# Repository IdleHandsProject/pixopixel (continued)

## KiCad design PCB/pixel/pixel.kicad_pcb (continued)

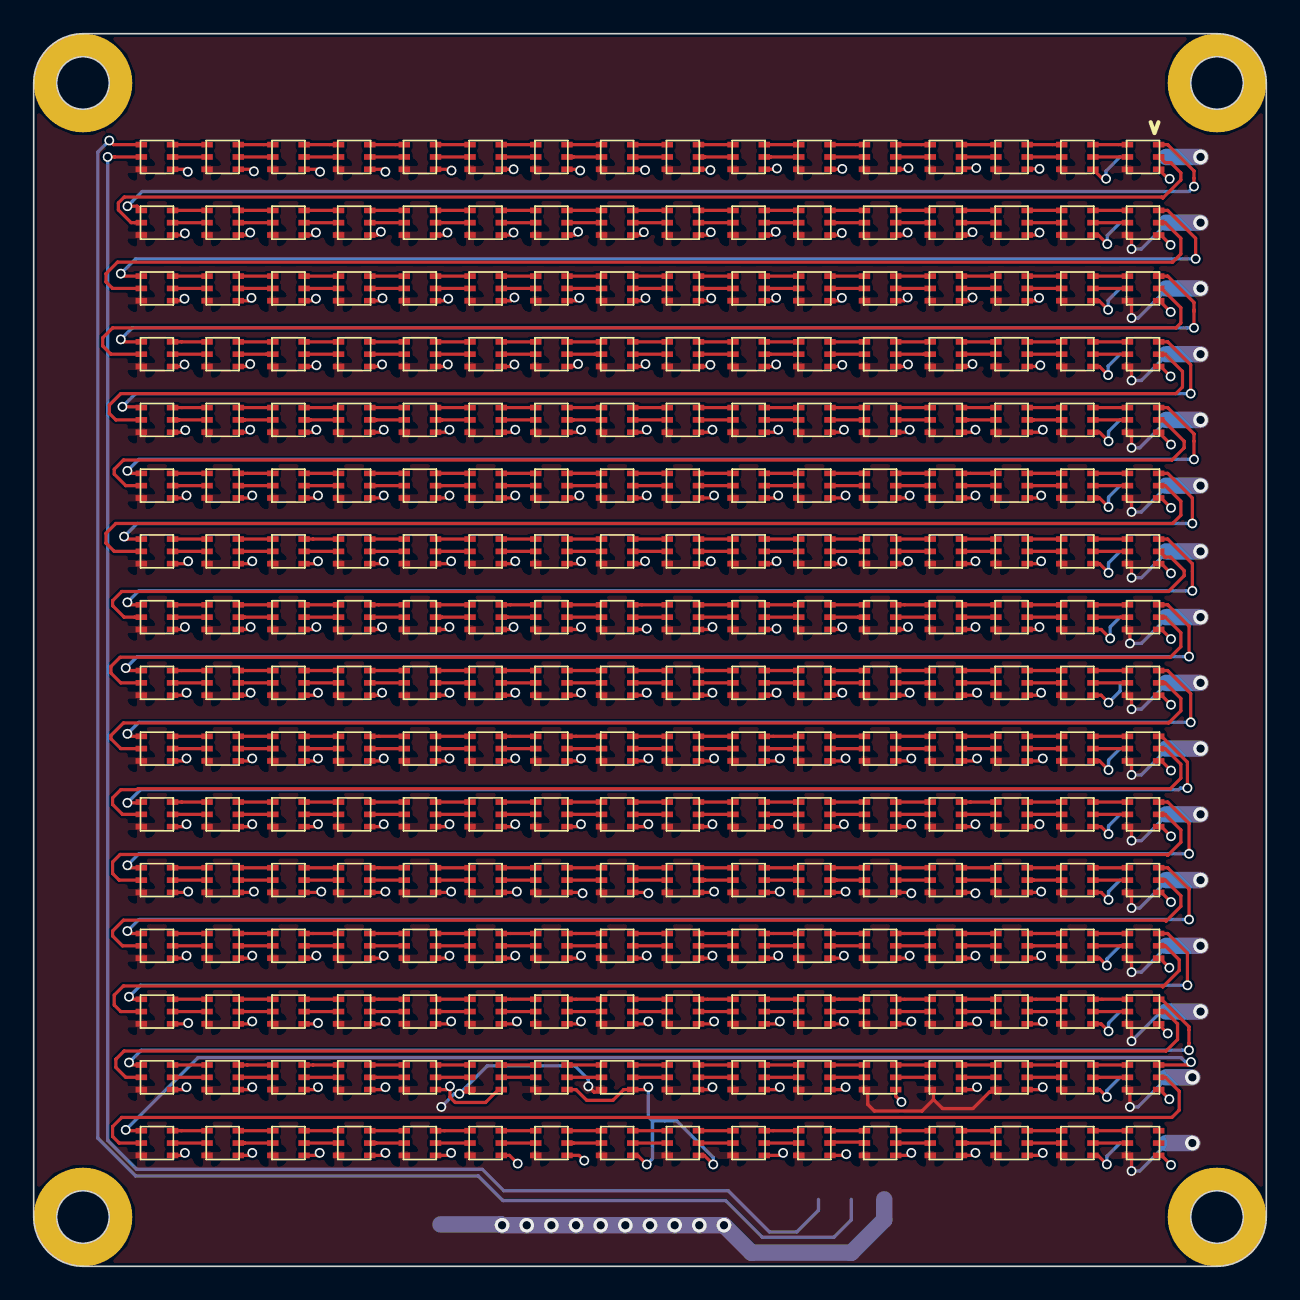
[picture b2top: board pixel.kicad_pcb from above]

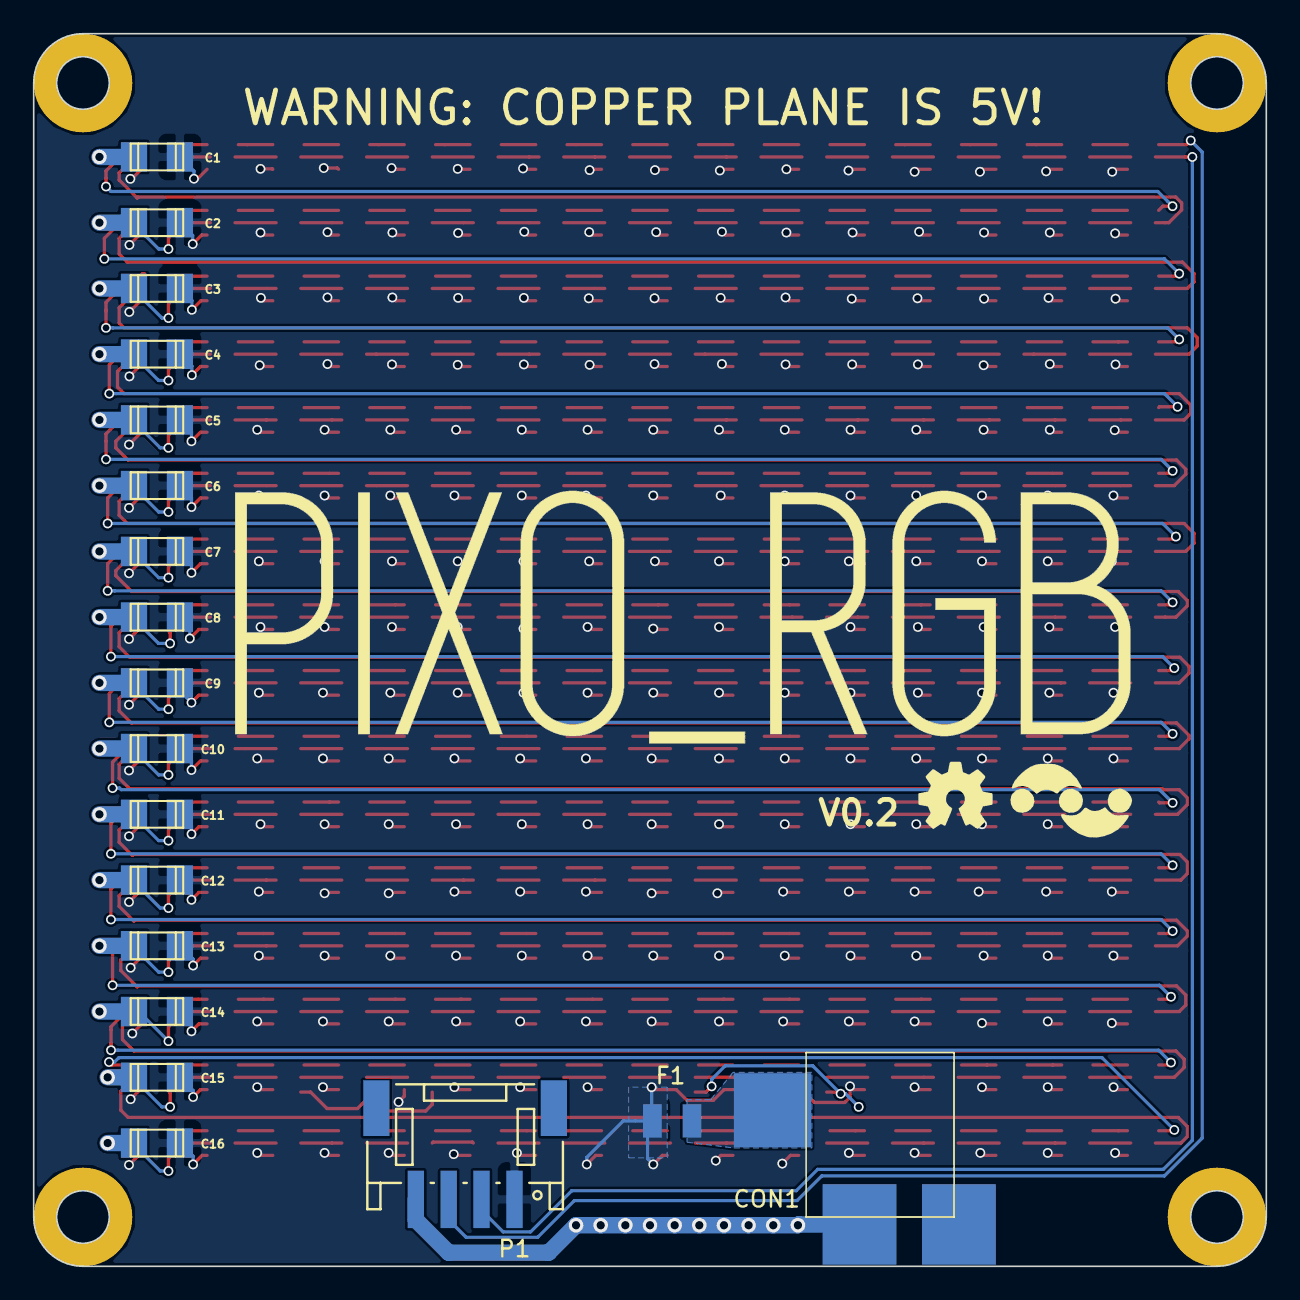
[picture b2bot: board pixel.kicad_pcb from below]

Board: 2 copper layers, 75.0 x 75.0 mm, 275 parts (19 on the bottom side), 515 nets.

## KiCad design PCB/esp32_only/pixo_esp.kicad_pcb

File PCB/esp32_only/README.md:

# ESPEverywhere
ESP8266 Special Make/100 Kickstarter Edition

Check out why this board exists here:
https://www.youtube.com/watch?v=67Kh_ikb-ds

The ESP Everywhere was made to take part in the Kickstarter Make/100 Campaign
You can get 1 of 100 boards assembled by me. Or you can Make your own.
Kickstarter is here:
https://www.kickstarter.com/projects/idlehandsdev/esp-everywhere-kickstarter-special-make-100

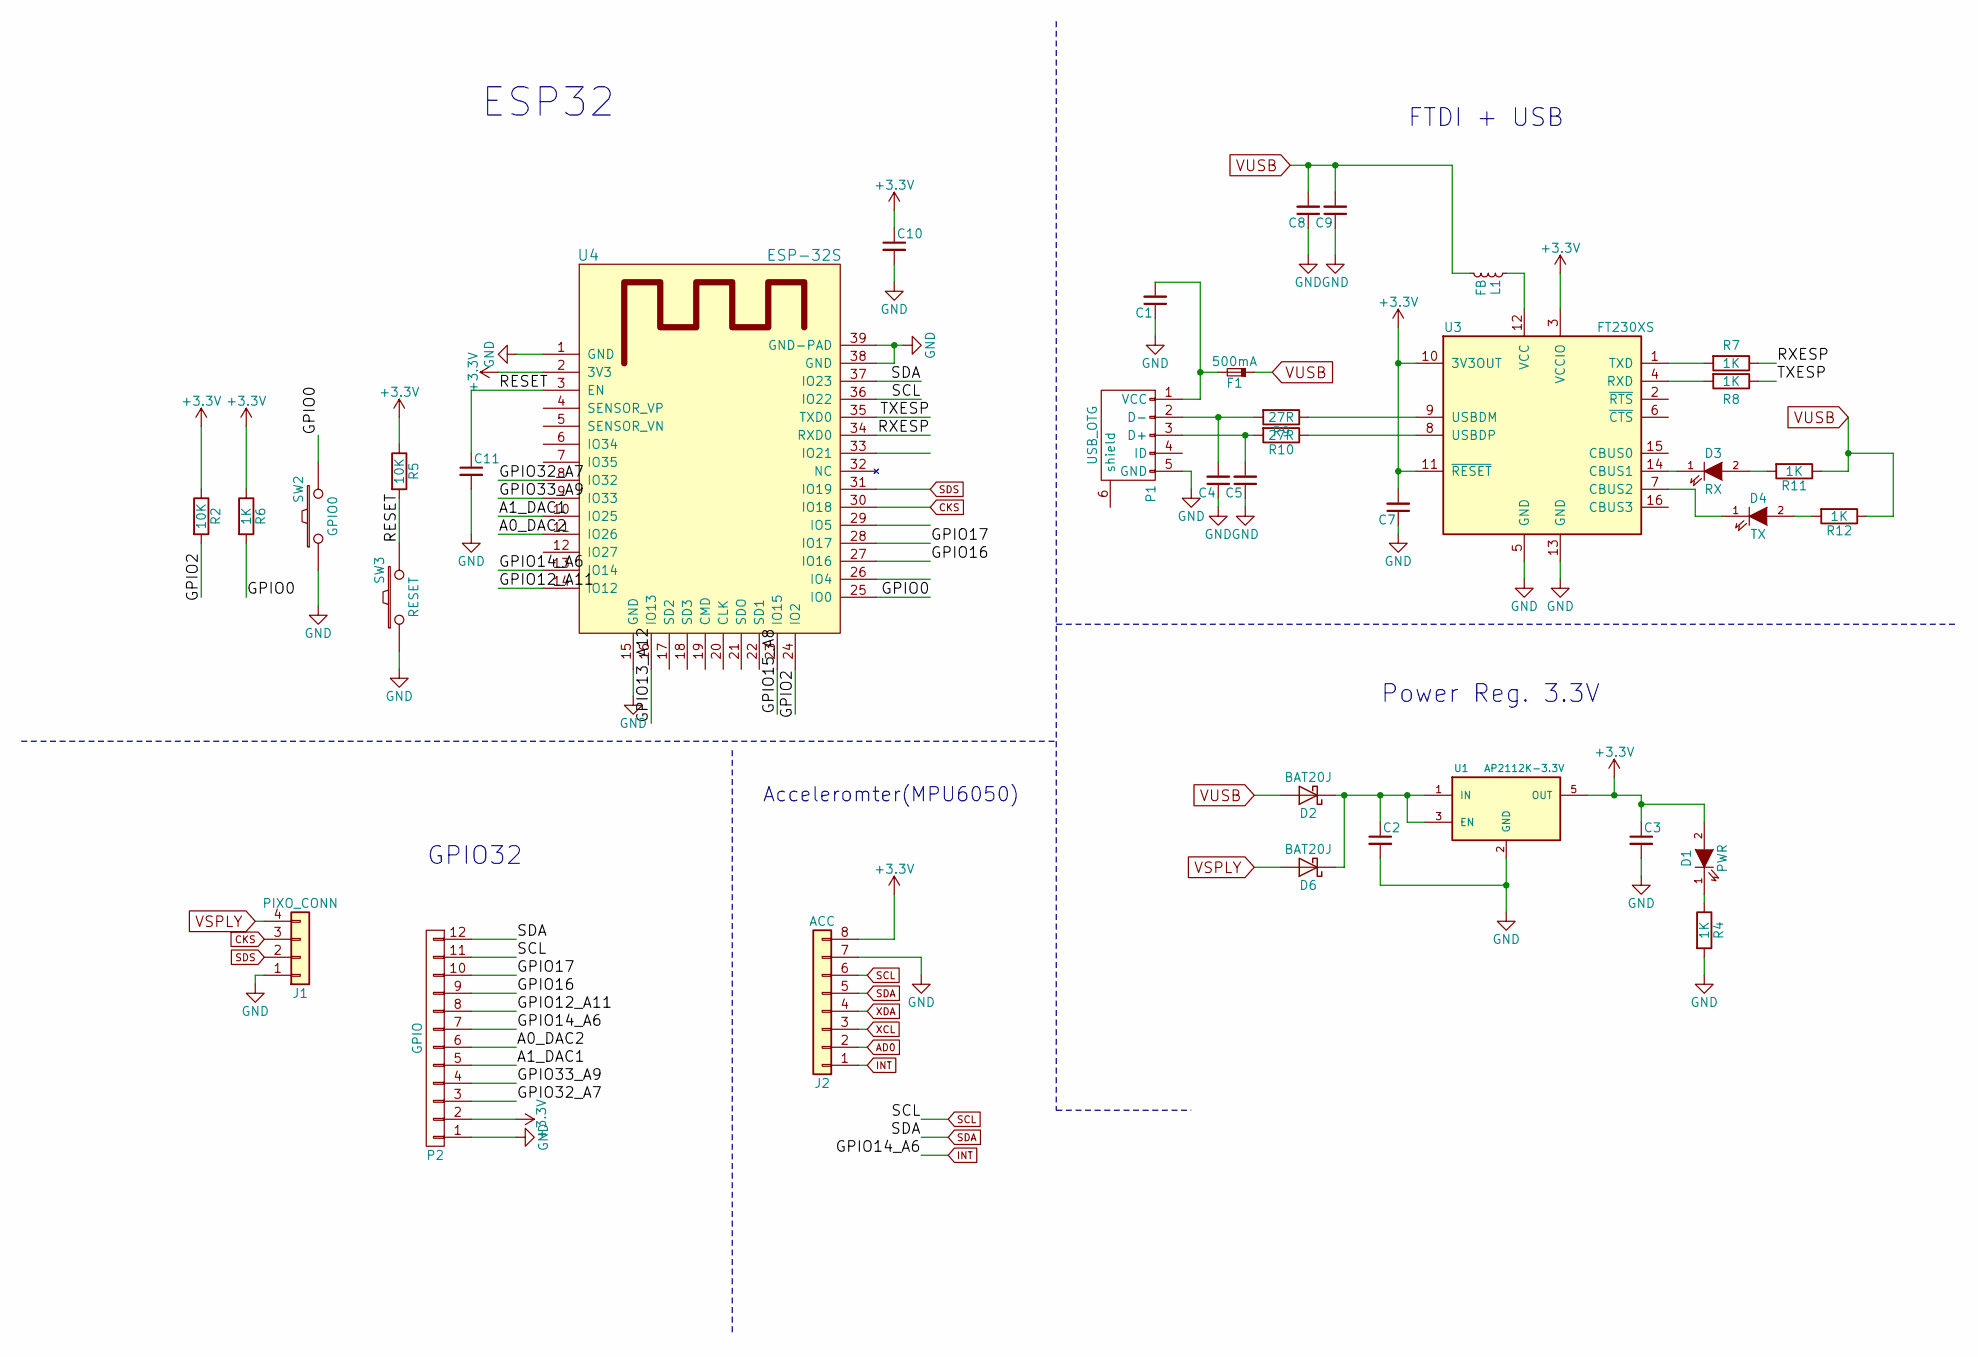
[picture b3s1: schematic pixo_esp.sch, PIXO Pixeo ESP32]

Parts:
C1, C7, C8: 0.1uF; C_0805; Digikey Part No. 1276-1003-1-ND
C2, C11: 1uF; C_0805; Digikey Part No. 311-1365-1-ND
C3: 2.2uF; C_0805; Digikey Part No. 490-3336-1-ND
C4, C5: 47pF; C_0805; Digikey Part No. 1276-1156-1-ND
C9: 10uF; C_0805; Digikey Part No. 1276-1003-1-ND
C10: 10uF; C_0805; Digikey Part No. 490-3340-1-ND
D1: PWR; Led_0603; Digikey Part No. 160-1447-1-ND
D2, D6: BAT20J; sod323; Digikey Part No. 497-3381-1-ND
D3: RX; Led_0603; Digikey Part No. 160-1448-1-ND
D4: TX; Led_0603; Digikey Part No. 160-1446-1-ND
F1: 500mA; c_1206; Digikey Part No. 507-1802-1-ND
J1: PIXO_CONN; Connectors_JST_S4B-PH-SM4-TB; Digikey Part No. 455-1751-1-ND
J2: ACC; Pin_Header_Straight_1x08; Digikey Part No. S7006-ND
L1: FB; R_0805_HandSoldering; Digikey Part No. 240-2390-1-ND
P1: USB_OTG; USB_Micro-B; Digikey Part No. 609-4618-1-ND
P2: GPIO; Pin_Header_Straight_1x12
R2, R5: 10K; R_0805; Digikey Part No. RR12P10.0KDCT-ND
R4, R6, R7, R8, R11, R12: 1K; R_0805; Digikey Part No. P1.0KDACT-ND
R9, R10: 27R; R_0805; Digikey Part No. RHM27KCT-ND
SW2: GPIO0; PTS-LFS; Digikey Part No. CKN9112CT-ND
SW3: RESET; PTS-LFS; Digikey Part No. CKN9112CT-ND
U1: AP2112K-3.3V; SOT-23-5; Digikey Part No. AP2112K-3.3TRG1DICT-ND
U3: FT230XS; SSOP-16_3.9x4.9mm_Pitch0.635mm; Digikey Part No. 768-1135-1-ND
U4: ESP-32S

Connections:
+3V3: C3.1, C7.2, C10.1, D1.2 (A), J2.8, P2.2, R2.1, R5.1, R6.1, U1.5 (OUT), U3.3 (VCCIO), U3.10 (3V3OUT), U3.11 (~RESET), U4.2 (3V3)
/A0_DAC2: P2.6, U4.11 (IO26)
/A1_DAC1: P2.5, U4.10 (IO25)
/GPIO0: R6.2, SW2.2, U4.25 (IO0)
/GPIO2: R2.2, U4.24 (IO2)
/GPIO12_A11: P2.8, U4.14 (IO12)
/GPIO13_A12: U4.16 (IO13)
/GPIO15_A8: U4.23 (IO15)
/GPIO16: P2.9, U4.27 (IO16)
/GPIO17: P2.10, U4.28 (IO17)
/GPIO32_A7: P2.3, U4.8 (IO32)
/GPIO33_A9: P2.4, U4.9 (IO33)
/RESET: C11.1, R5.2, SW3.2, U4.3 (EN)
/RXESP: R7.1, U4.34 (RXD0)
/TXESP: R8.1, U4.35 (TXD0)
AD0: J2.2
CKS: J1.3, U4.30 (IO18)
GND: C1.1, C2.2, C3.2, C4.1, C5.1, C7.1, C8.1, C9.1, C10.2, C11.2, J1.1, J2.7, P1.5 (GND), P2.1, R4.2, SW2.1, SW3.1, U1.2 (GND), U3.5 (GND), U3.13 (GND), U4.1 (GND), U4.15 (GND), U4.38 (GND), U4.39 (GND-PAD)
INT: J2.1, P2.7, U4.13 (IO14)
unnamed: C1.2, F1.2, P1.1 (VCC)
unnamed: C2.1, D2.1 (K), D6.1 (K), U1.1 (IN), U1.3 (EN)
unnamed: C4.2, P1.2 (D-), R9.2
unnamed: C5.2, P1.3 (D+), R10.2
unnamed: D1.1 (K), R4.1
unnamed: D3.1 (K), U3.14 (CBUS1)
unnamed: D3.2 (A), R11.2
unnamed: D4.1 (K), U3.7 (CBUS2)
unnamed: D4.2 (A), R12.2
unnamed: L1.1, U3.12 (VCC)
unnamed: R7.2, U3.1 (TXD)
unnamed: R8.2, U3.4 (RXD)
unnamed: R9.1, U3.9 (USBDM)
unnamed: R10.1, U3.8 (USBDP)
SCL: J2.6, P2.11, U4.36 (IO22)
SDA: J2.5, P2.12, U4.37 (IO23)
SDS: J1.2, U4.31 (IO19)
VSPLY: D6.2 (A), J1.4
VUSB: C8.2, C9.2, D2.2 (A), F1.1, L1.2, R11.1, R12.1
XCL: J2.3
XDA: J2.4

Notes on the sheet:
FTDI + USB
Power Reg. 3.3V
ESP32
GPIO32
Acceleromter(MPU6050)

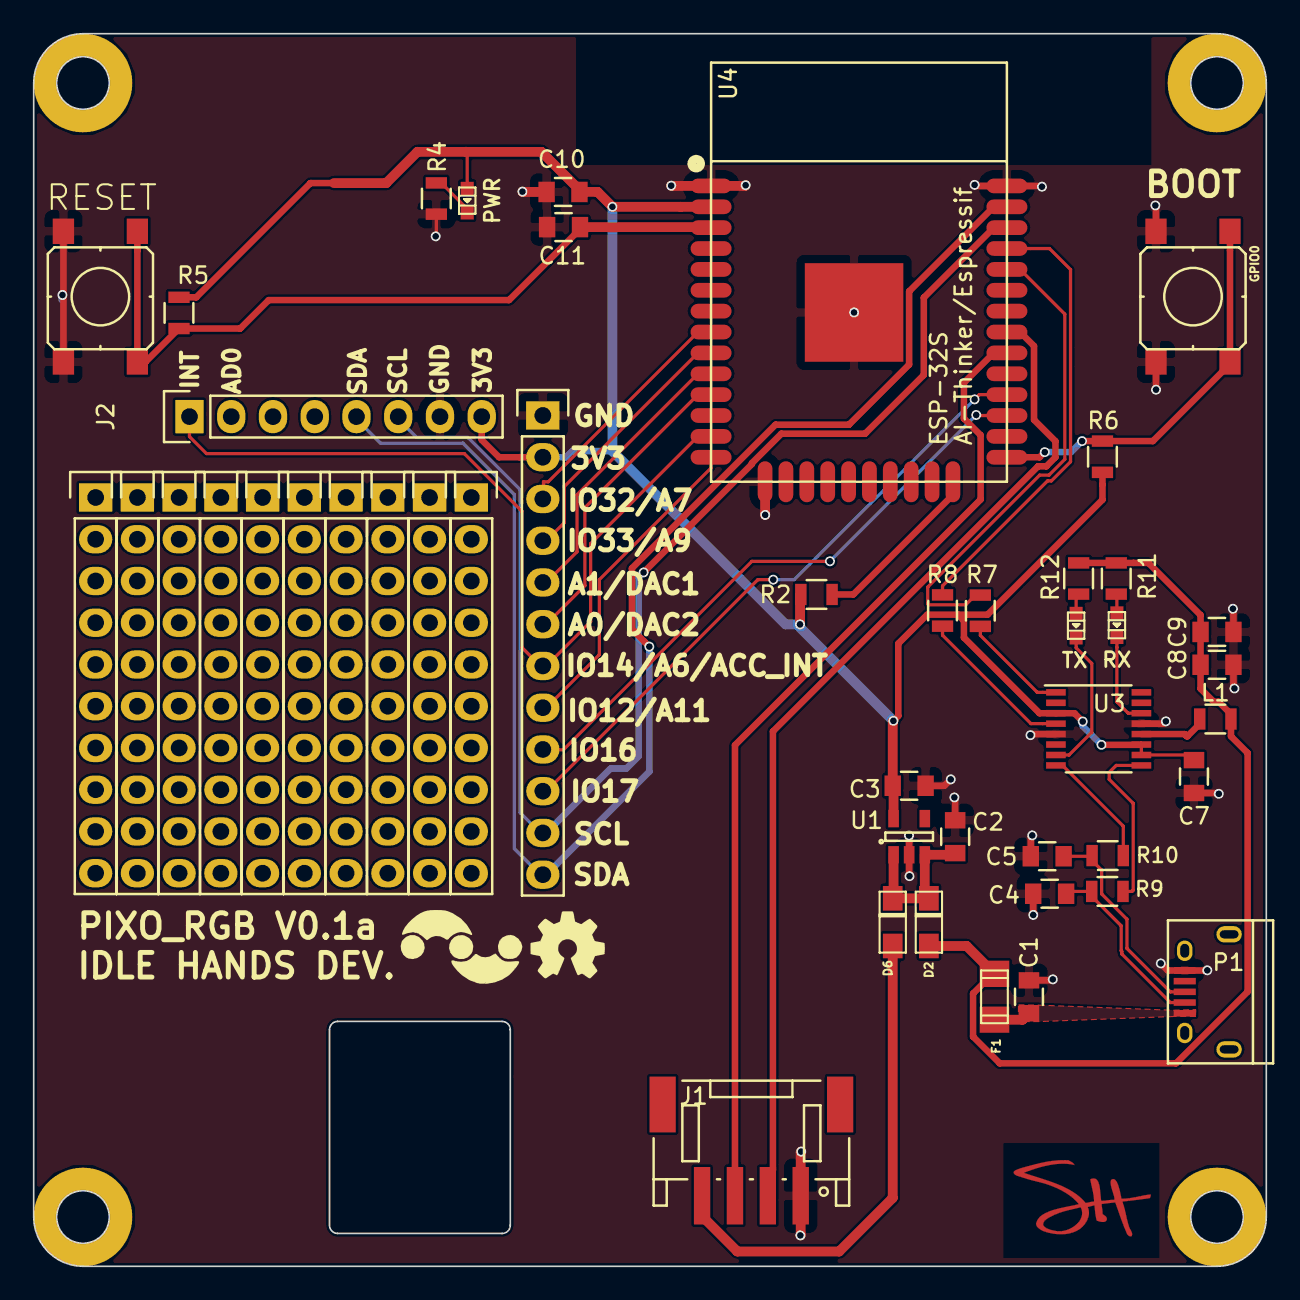
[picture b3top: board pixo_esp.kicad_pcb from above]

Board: 2 copper layers, 75.0 x 75.0 mm, 36 parts (0 on the bottom side), 35 nets.

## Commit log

2018-01-31 added initial files, need some changes
2018-02-01 added rough sample firmware
2018-02-14 New Firmware and Python Script
2018-02-21 added fuse, fixed traces
2018-02-21 added accelerometer, changed GPIO
2018-02-21 widened keepout for antenna
2018-05-12 changed led pad layout
2018-06-21 Programs added
2018-06-21 LED Layout Modified
2018-06-21 updated BOM and small fixes
2018-06-23 Added Case directory with a 3D printable case
2018-06-28 added dxf files of boards
2018-07-05 Add some flashing instructions
2018-07-05 Add Kickstarter section
2018-07-05 Add sean's programming demo video
2018-07-05 Add instructions for patching i2cdev and mpu6050
2018-07-05 Minor semantic changes
2018-07-24 Update README
    The pull request to have the board built into the
    Arduino ESP32 hardware was closed for inactivity - Just Adafruit ESP32 Feather
    The ESP32 hardware's master branch is no longer broken
    and thus the workaround is no longer required - Install as normall per their instructions
2018-07-25 Semantic change for consistency among functions
    Introduce "Pixol" term to describe the resulting array
    from converting an image file
2018-07-25 Add randChangeImage -INCOMPLETE
2018-07-25 Updated example usage of the functions
    The scrolling animations appear to have broken
    in the second stage, where the image is scrolling out of view.
2018-07-25 Add optional color selection defined via the PXL structure
    This can be useful for using the same icon with a different color
    to indicate various states
2018-07-25 Various cleanup
2018-07-25 Add Upward-Scrolling Notification
    This will scroll an image up into view, pause briefly (dlytime),
    and continue scrolling upwards. This also takes a `loop` argument
    that dictates how many times it should scroll
2018-07-25 Fixed randChangePxl to now use the PXL structure
    This allows the animation to happen very quickly without consuming
    all the resources while waiting for an approiate random number
2018-07-25 Add "Scanline"-style image transition
    This will switch the display from one image to
    another, one pixel at a time. The speed can be controlled via
    the `anitime` argument.
2018-07-25 Add a Struct to manage the pixels
2018-07-25 Add notifyBlinkPxl
    A simple animation to "blink" an image
2018-07-25 Define a global number of pixels for code flexibility
2018-07-25 light cleanup
2018-07-25 Add example to contain various display helper functions
2018-07-25 Add popup notification
    This scrolls an image up into view,
    and back down out of view after the delay
2018-07-25 Update gitignore
2018-07-25 it me :3
2018-07-25 Show a pixo-icon on screen for a delayed amount of time
2018-10-30 add missing icon (wifi)
